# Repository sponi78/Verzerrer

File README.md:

# Verzerrer

Basic circuit for a distortion circuit.

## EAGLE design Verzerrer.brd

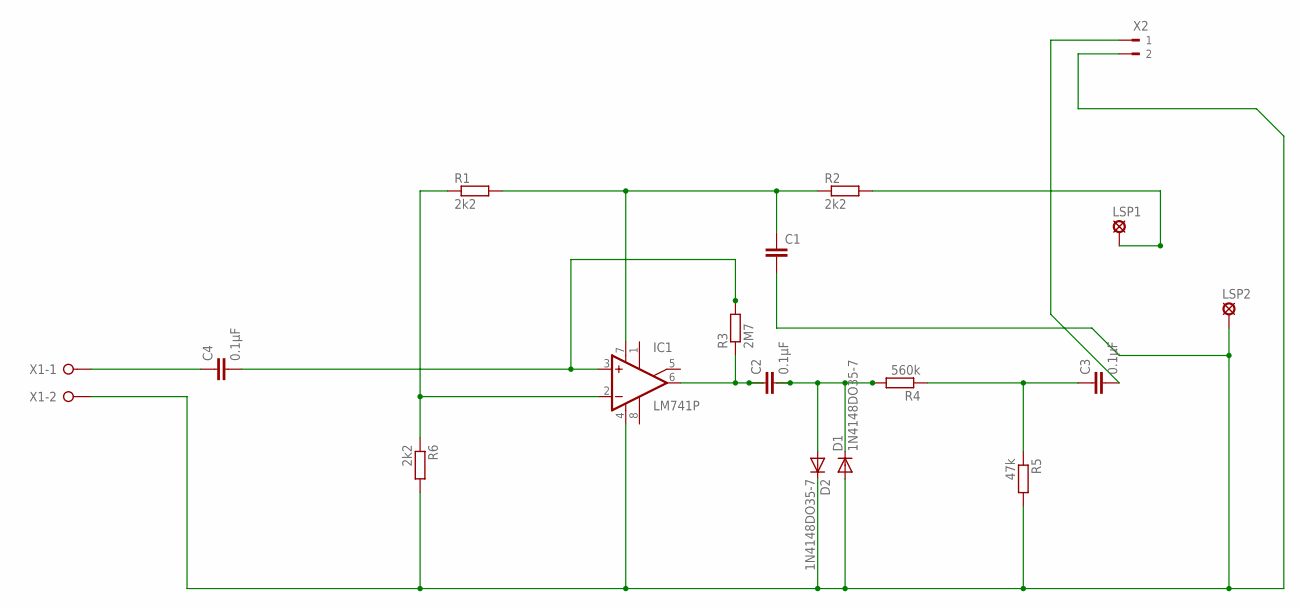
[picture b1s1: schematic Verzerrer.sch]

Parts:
C1: C5/2.5; C5B2.5
C2, C3, C4: 0.1µF; C5B2.5
D1, D2: 1N4148DO35-7; DO35-7
IC1: LM741P; DIL08
LSP1, LSP2: LSP11
R1, R2, R6: 2k2; 0207/10
R3: 2M7; 0207/10
R4: 560k; 0207/10
R5: 47k; 0207/10
X1: W237-2N
X2: 180-2

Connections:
unnamed: IC1.2 (-IN), R1.1, R6.1
unnamed: C2.1, IC1.6 (OUT), R3.1
unnamed: C2.2, D1.C, D2.A, R4.2
unnamed: C4.2, IC1.3 (+IN), R3.2
unnamed: LSP1.MP, R2.2
unnamed: C1.1, IC1.7 (V+), R1.2, R2.1
unnamed: C1.2, D1.A, D2.C, IC1.4 (V-), LSP2.MP, R5.2, R6.2, X1.2, X2.2
unnamed: C3.1, R4.1, R5.1
unnamed: C3.2, X2.1
unnamed: C4.1, X1.1

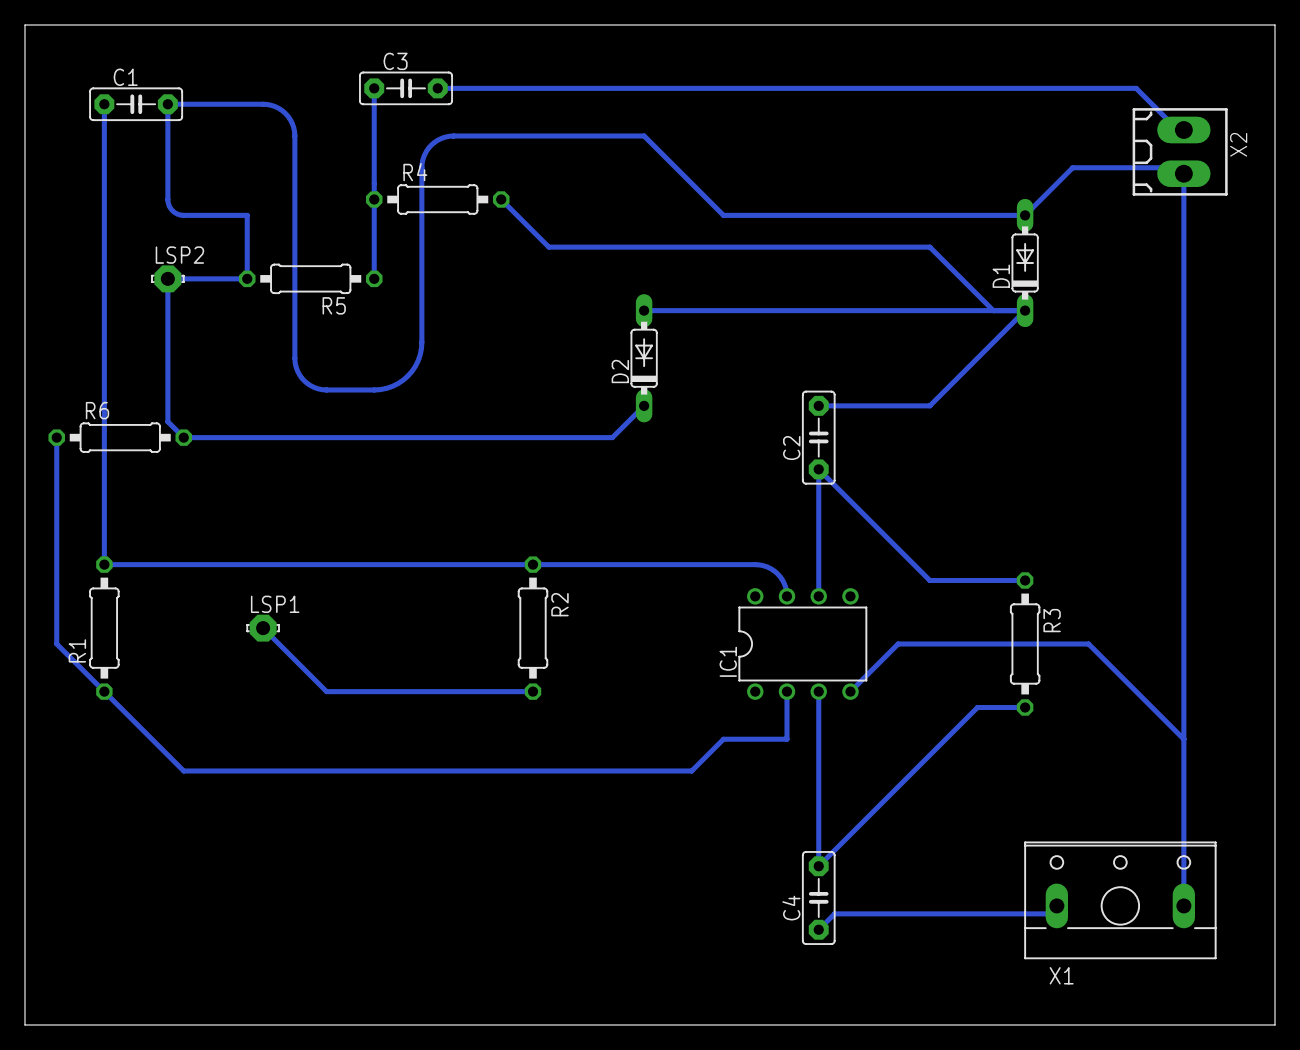
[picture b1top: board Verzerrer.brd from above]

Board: 2 copper layers, 100.0 x 80.0 mm, 17 parts (0 on the bottom side), 10 nets.

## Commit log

2016-04-06 first release
2016-04-06 Board bearbeitet
2016-04-06 with images
